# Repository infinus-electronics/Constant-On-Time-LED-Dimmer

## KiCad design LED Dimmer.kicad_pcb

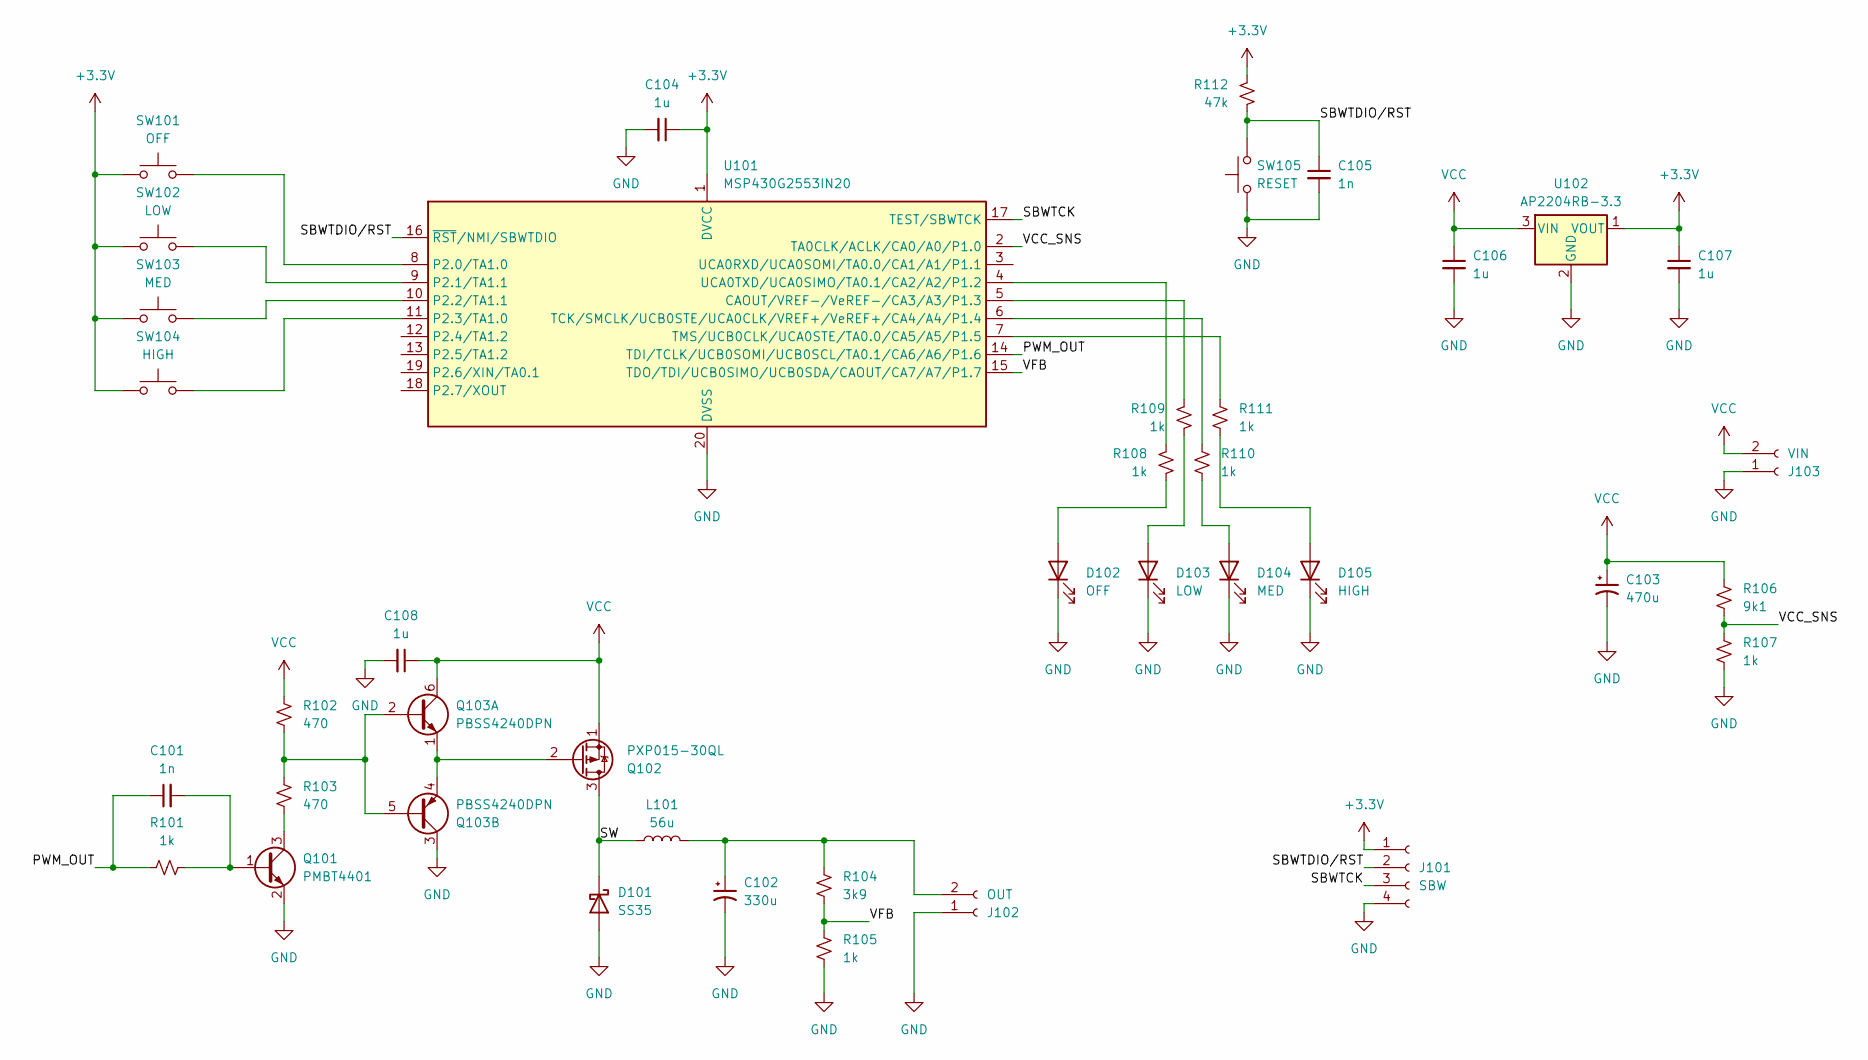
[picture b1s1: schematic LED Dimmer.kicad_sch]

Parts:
C101, C105: 1n; C_0402_1005Metric_Pad0.74x0.62mm_HandSolder
C102: 330u; CP_Elec_8x10; Part Number UWT1E331MNL1GS
C103: 470u; CP_Elec_8x10
C104, C106, C107, C108: 1u; C_0402_1005Metric_Pad0.74x0.62mm_HandSolder
D101: SS35; D_SMC_Handsoldering
D102: OFF; D_0805_2012Metric_Pad1.15x1.40mm_HandSolder
D103: LOW; D_0805_2012Metric_Pad1.15x1.40mm_HandSolder
D104: MED; D_0805_2012Metric_Pad1.15x1.40mm_HandSolder
D105: HIGH; D_0805_2012Metric_Pad1.15x1.40mm_HandSolder
J101: SBW; PinHeader_1x04_P2.54mm_Vertical
J102: OUT; TerminalBlock_bornier-2_P5.08mm
J103: VIN; TerminalBlock_bornier-2_P5.08mm
L101: 56u; L_Bourns_SRR1208_12.7x12.7mm; Part Number HCM1A1307V2-560-R
Q101: PMBT4401; SOT-23_Handsoldering
Q102: PXP015-30QL; PXP01530QLJ
Q103: PBSS4240DPN; TSOT-23-6_HandSoldering
R101, R105, R107, R108, R109, R110, R111: 1k; R_0805_2012Metric_Pad1.20x1.40mm_HandSolder
R102, R103: 470; R_2010_5025Metric; Part Number RC2010JK-07470RL
R104: 3k9; R_0805_2012Metric_Pad1.20x1.40mm_HandSolder
R106: 9k1; R_0805_2012Metric_Pad1.20x1.40mm_HandSolder
R112: 47k; R_0805_2012Metric_Pad1.20x1.40mm_HandSolder
SW101: OFF; SW_PUSH_6mm
SW102: LOW; SW_PUSH_6mm
SW103: MED; SW_PUSH_6mm
SW104: HIGH; SW_PUSH_6mm
SW105: RESET; SW_PUSH_6mm
U101: MSP430G2553IN20; DIP-20_W7.62mm
U102: AP2204RB-3.3; SOT-89-3

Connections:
+3.3V: C104.1, C107.1, J101.1, R112.1, SW101.1, SW102.1, SW103.1, SW104.1, U101.1 (DVCC), U102.1 (VOUT)
/PWM_OUT: C101.1, R101.1, U101.14 (TDI/TCLK/UCB0SOMI/UCB0SCL/TA0.1/CA6/A6/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)
/SBWTCK: J101.3, U101.17 (TEST/SBWTCK)
/SBWTDIO/RST: C105.1, J101.2, R112.2, SW105.2, U101.16 (~RST/NMI/SBWTDIO)
/SW: D101.1 (K), L101.1, Q102.3 (D)
/VCC_SNS: R106.2, R107.1, U101.2 (TA0CLK/ACLK/CA0/A0/P1.0)
/VFB: R104.2, R105.1, U101.15 (TDO/TDI/UCB0SIMO/UCB0SDA/CAOUT/CA7/A7/P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)
GND: C102.2, C103.2, C104.2, C105.2, C106.2, C107.2, C108.2, D101.2 (A), D102.1 (K), D103.1 (K), D104.1 (K), D105.1 (K), J101.4, J102.1, J103.1, Q101.2 (E), Q103.3 (C2), R105.2, R107.2, SW105.1, U101.20 (DVSS), U102.2 (GND)
unnamed: D102.2 (A), R108.2
unnamed: D103.2 (A), R109.2
unnamed: D104.2 (A), R110.2
unnamed: D105.2 (A), R111.2
unnamed: C102.1, J102.2, L101.2, R104.1
unnamed: C101.2, Q101.1 (B), R101.2
unnamed: Q101.3 (C), R103.1
unnamed: Q102.2 (G), Q103.1 (E1), Q103.4 (E2)
unnamed: Q103.2 (B1), Q103.5 (B2), R102.1, R103.2
unnamed: R109.1, U101.5 (CAOUT/VREF-/VeREF-/CA3/A3/P1.3)
unnamed: SW101.2, U101.8 (P2.0/TA1.0)
unnamed: SW102.2, U101.9 (P2.1/TA1.1)
unnamed: SW103.2, U101.10 (P2.2/TA1.1)
unnamed: SW104.2, U101.11 (P2.3/TA1.0)
unnamed: R110.1, U101.6 (TCK/SMCLK/UCB0STE/UCA0CLK/VREF+/VeREF+/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)
unnamed: R111.1, U101.7 (TMS/UCB0CLK/UCA0STE/TA0.0/CA5/A5/P1.5)
unnamed: R108.1, U101.4 (UCA0TXD/UCA0SIMO/TA0.1/CA2/A2/P1.2)
VCC: C103.1, C106.1, C108.1, J103.2, Q102.1 (S), Q103.6 (C1), R102.2, R106.1, U102.3 (VIN)

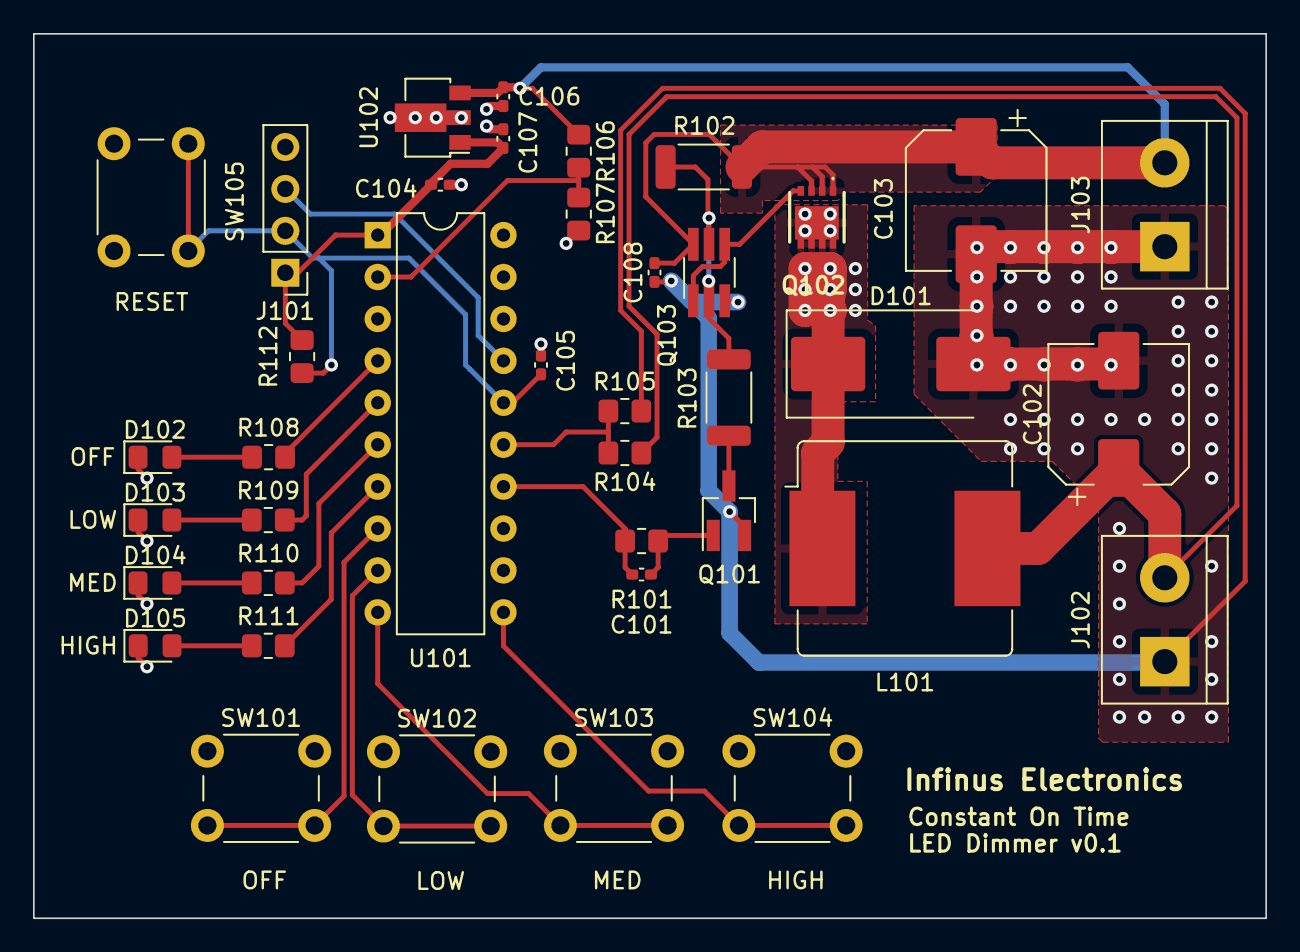
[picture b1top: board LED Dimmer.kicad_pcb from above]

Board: 2 copper layers, 74.7 x 53.6 mm, 39 parts (0 on the bottom side), 26 nets.

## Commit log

2024-01-25 init
2024-01-25 firmware
